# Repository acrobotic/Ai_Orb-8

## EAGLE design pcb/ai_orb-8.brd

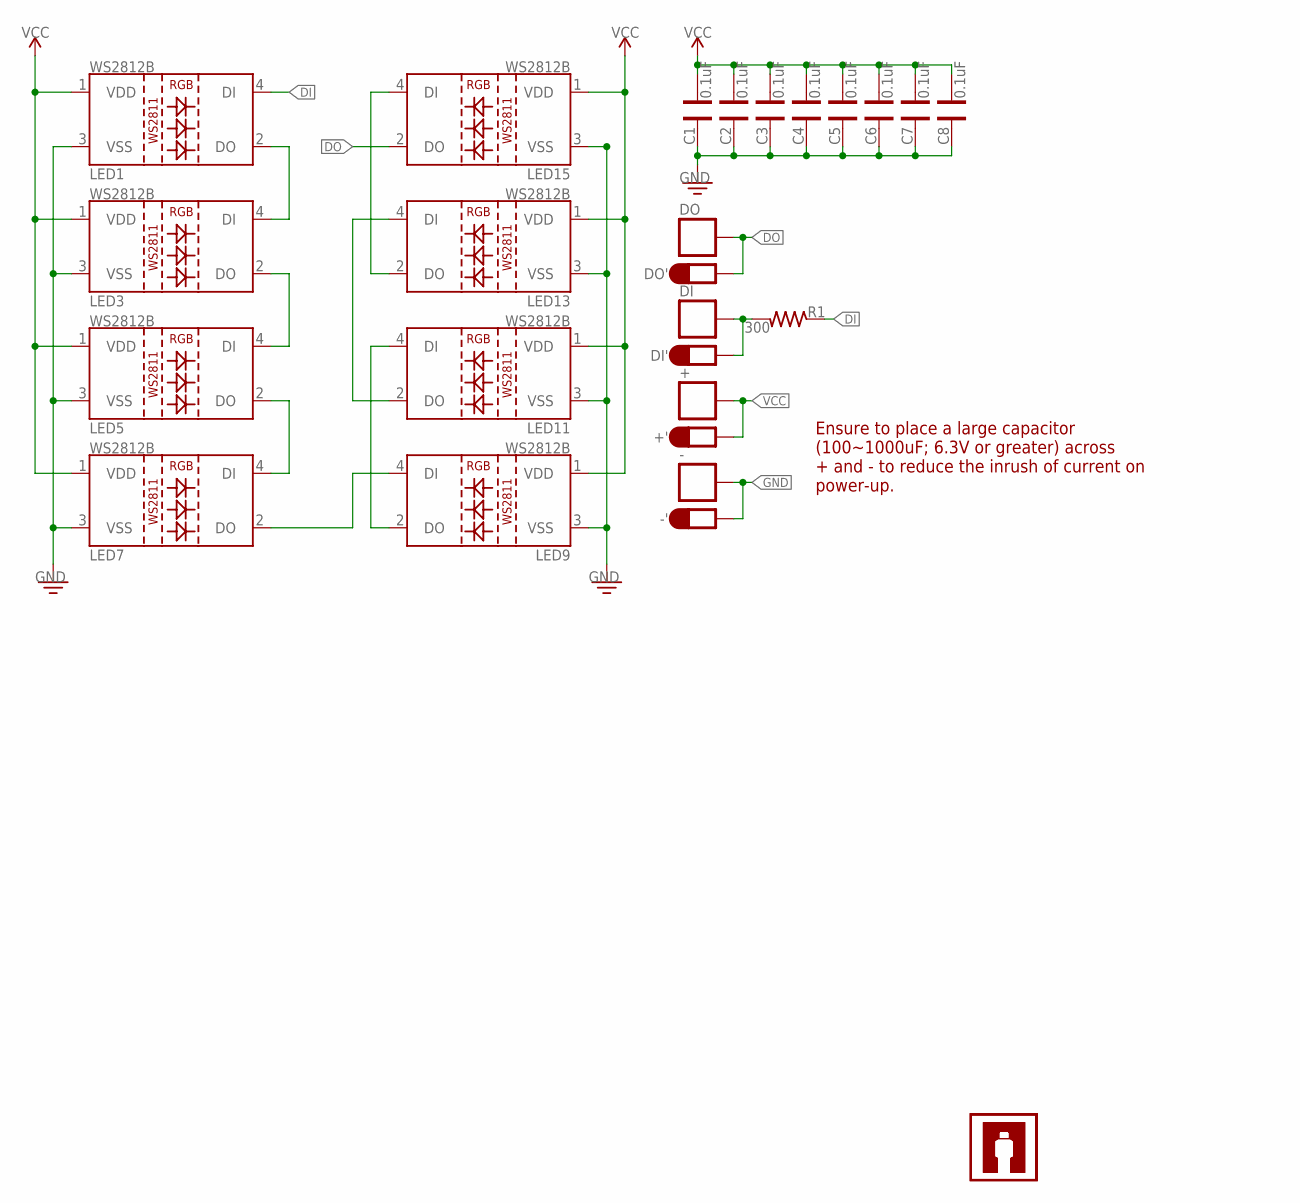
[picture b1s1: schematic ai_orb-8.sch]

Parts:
+: 1X01-SM
+': 1X01-PETAL
-: 1X01-SM
-': 1X01-PETAL
C1, C2, C3, C4, C5, C6, C7, C8: 0.1uF; CAP-0402
DI: 1X01-SM
DI': 1X01-PETAL
DO: 1X01-SM
DO': 1X01-PETAL
LED1, LED3, LED5, LED7, LED9, LED11, LED13, LED15: LED-WS2812B-SM
LOGO, LOGO1: AI-LOGOXS; AI-LOGO-XS
R1: 300; RES-0402

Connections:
DI: LED1.4 (DI), R1.1
DO: DO.1, DO'.1, LED15.2 (DO)
GND: -.1, -'.1, C1.2, C2.2, C3.2, C4.2, C5.2, C6.2, C7.2, C8.2, LED1.3 (VSS), LED3.3 (VSS), LED5.3 (VSS), LED7.3 (VSS), LED9.3 (VSS), LED11.3 (VSS), LED13.3 (VSS), LED15.3 (VSS)
unnamed: LED1.2 (DO), LED3.4 (DI)
unnamed: DI.1, DI'.1, R1.2
unnamed: LED3.2 (DO), LED5.4 (DI)
unnamed: LED5.2 (DO), LED7.4 (DI)
unnamed: LED7.2 (DO), LED9.4 (DI)
unnamed: LED9.2 (DO), LED11.4 (DI)
unnamed: LED11.2 (DO), LED13.4 (DI)
unnamed: LED13.2 (DO), LED15.4 (DI)
VCC: +.1, +'.1, C1.1, C2.1, C3.1, C4.1, C5.1, C6.1, C7.1, C8.1, LED1.1 (VDD), LED3.1 (VDD), LED5.1 (VDD), LED7.1 (VDD), LED9.1 (VDD), LED11.1 (VDD), LED13.1 (VDD), LED15.1 (VDD)

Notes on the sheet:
Ensure to place a large capacitor (100~1000uF; 6.3V or greater) across + and - to reduce the inrush of current on power-up.

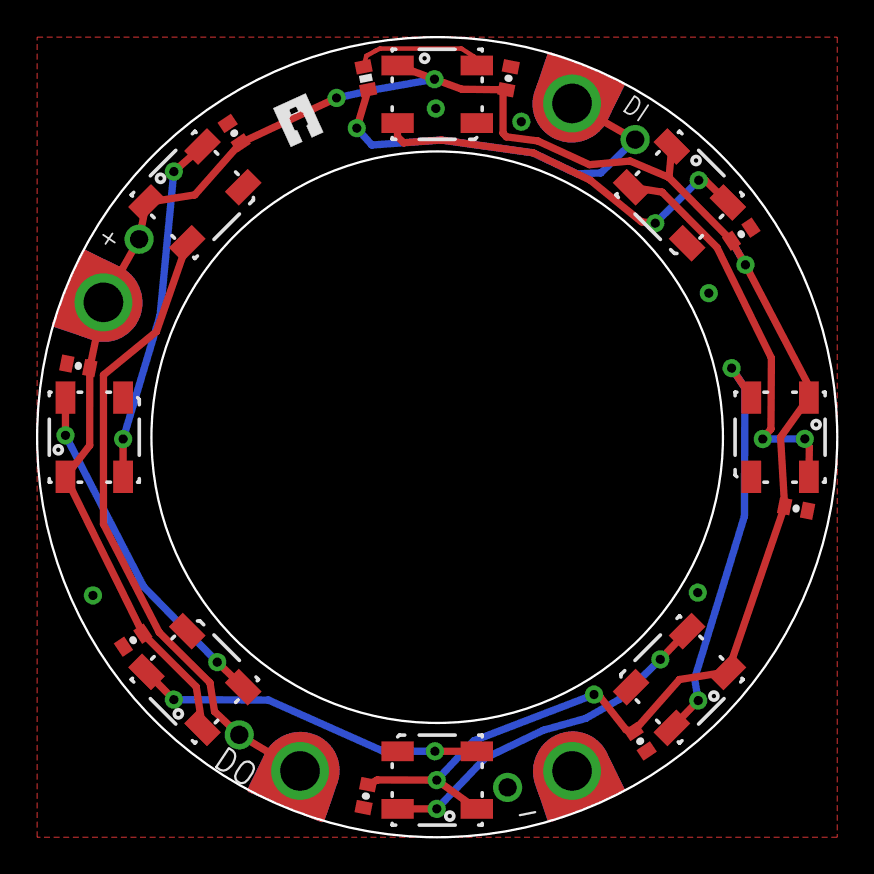
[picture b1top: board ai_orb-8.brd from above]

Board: 2 copper layers, 44.5 x 44.5 mm, 27 parts (1 on the bottom side), 12 nets.

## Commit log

2014-11-30 updating
2014-12-29 updating files
2015-06-29 minor fix on silkscreen
